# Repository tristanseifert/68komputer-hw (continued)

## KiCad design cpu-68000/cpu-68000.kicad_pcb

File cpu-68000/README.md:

# 68000 CPU Board
This directory contains the schematic and board files for the main 68komputer CPU board, based around a 68000 operating at up to 10MHz. It combines the processor with 1M of RAM and flash ROM and some additional peripherals.

## Peripherals
In addition to the megabyte of boot ROM and RAM available on the board, the following peripherals are available:

- 32K of battery backed NVRAM, which includes a phantom RTC for time keeping
- An [XR68C681](https://www.maxlinear.com/product/interface/uarts/8-bit-vlio-uarts/xr68c681) DUART, compatible with the "legacy" Motorola 68681 part
- I²C master provided by a [PCF8584](https://www.nxp.com/products/interfaces/ic-spi-serial-interface-devices/ic-bus-controller-and-bridge-ics/ic-bus-controller:PCF8584) controller. It's used to access the I2C bus on the backplane.
- Dual SAA1099 PSG audio chips

## Backplane Interface
The backplane interface is just a buffered copy of the 68k's address and data bus, as well as many of its control signals. The direction of buffers on the CPU board are automatically controlled taking into account external bus masters.

As long as external bus masters properly implement the 68000 bus mastering, they will be entirely transparent. All read/write transactions to peripherals implemented on the CPU board itself will be broadcast on the backplane bus to allow external debugging hardware to capture these accesses.

## Programmable Logic
Many of the logic parts of the system are implemented in 22V10C GALs. See the `logic` directory for these files. They can be assembled using [galette.](https://github.com/simon-frankau/galette)

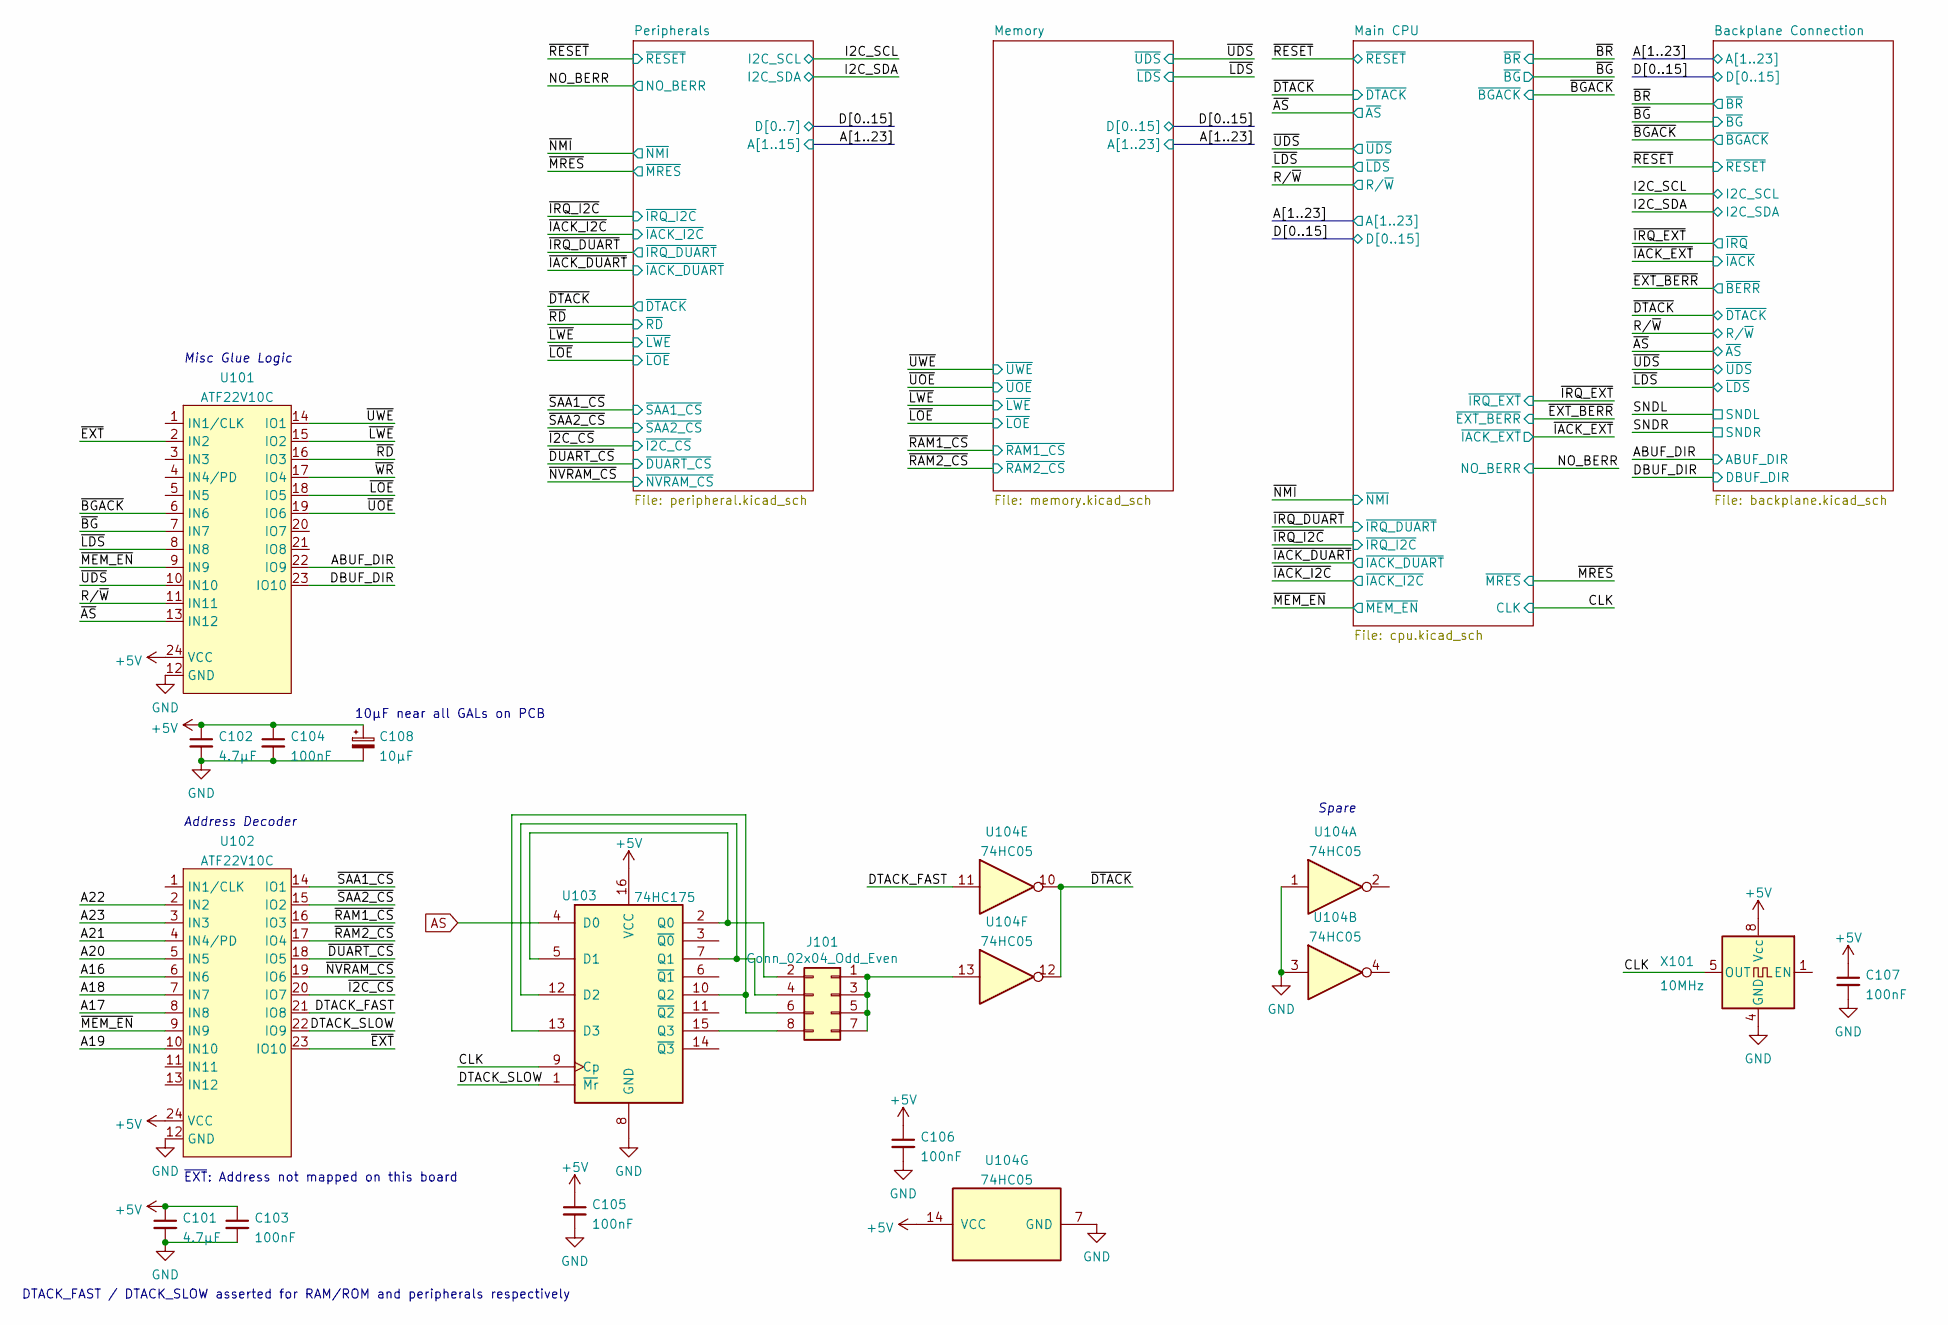
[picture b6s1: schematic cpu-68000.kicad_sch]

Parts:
C101, C102: 4.7µF; C_0805_2012Metric
C103, C104, C105, C106, C107: 100nF; C_0805_2012Metric
C108: 10µF; CP_EIA-3216-18_Kemet-A
J101: Conn_02x04_Odd_Even; PinHeader_2x04_P2.54mm_Vertical
U101, U102: ATF22V10C; DIP-24_W7.62mm_Socket
U103: 74HC175; TSSOP-16_4.4x5mm_P0.65mm; MPN 74HC175PW,118
U104: 74HC05; SOIC-14_3.9x8.7mm_P1.27mm
X101: 10MHz; Oscillator_DIP-8

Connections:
+5V: C101.1, C102.1, C103.1, C104.1, C105.1, C106.1, C107.1, C108.1, U101.24 (VCC), U102.24 (VCC), U103.16 (VCC), U104.14 (VCC), X101.8 (Vcc); also elsewhere on the board
/A16: U102.6 (IN6); also elsewhere on the board
/A17: U102.8 (IN8); also elsewhere on the board
/A18: U102.7 (IN7); also elsewhere on the board
/A19: U102.10 (IN10); also elsewhere on the board
/A20: U102.5 (IN5); also elsewhere on the board
/A21: U102.4 (IN4/PD); also elsewhere on the board
/A22: U102.2 (IN2); also elsewhere on the board
/A23: U102.3 (IN3); also elsewhere on the board
/ABUF_DIR: U101.22 (IO9); also elsewhere on the board
/CLK: U103.9 (Cp), X101.5 (OUT); also elsewhere on the board
/DBUF_DIR: U101.23 (IO10); also elsewhere on the board
/DTACK_FAST: U102.21 (IO8), U104.11
/DTACK_SLOW: U102.22 (IO9), U103.1 (~Mr)
/R/~W: U101.11 (IN11); also elsewhere on the board
/~AS: U101.13 (IN12); also elsewhere on the board
/~BGACK: U101.6 (IN6); also elsewhere on the board
/~BG: U101.7 (IN7); also elsewhere on the board
/~DTACK: U104.10, U104.12; also elsewhere on the board
/~DUART_CS: U102.18 (IO5); also elsewhere on the board
/~EXT: U101.2 (IN2), U102.23 (IO10)
/~I2C_CS: U102.20 (IO7); also elsewhere on the board
/~LDS: U101.8 (IN8); also elsewhere on the board
/~LOE: U101.18 (IO5); also elsewhere on the board
/~LWE: U101.15 (IO2); also elsewhere on the board
/~MEM_EN: U101.9 (IN9), U102.9 (IN9); also elsewhere on the board
/~NVRAM_CS: U102.19 (IO6); also elsewhere on the board
/~RAM1_CS: U102.16 (IO3); also elsewhere on the board
/~RAM2_CS: U102.17 (IO4); also elsewhere on the board
/~RD: U101.16 (IO3)
/~SAA1_CS: U102.14 (IO1); also elsewhere on the board
/~SAA2_CS: U102.15 (IO2); also elsewhere on the board
/~UDS: U101.10 (IN10); also elsewhere on the board
/~UOE: U101.19 (IO6); also elsewhere on the board
/~UWE: U101.14 (IO1); also elsewhere on the board
/~WR: U101.17 (IO4)
AS: U103.4 (D0); also elsewhere on the board
GND: C101.2, C102.2, C103.2, C104.2, C105.2, C106.2, C107.2, C108.2, U101.12 (GND), U102.12 (GND), U103.8 (GND), U104.1, U104.3, U104.7 (GND), X101.4 (GND); also elsewhere on the board
unnamed: J101.1, J101.3, J101.5, J101.7, U104.13
unnamed: J101.2, U103.2 (Q0), U103.5 (D1)
unnamed: J101.4, U103.7 (Q1), U103.12 (D2)
unnamed: J101.6, U103.10 (Q2), U103.13 (D3)
unnamed: J101.8, U103.15 (Q3)

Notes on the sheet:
Address Decoder
~{EXT}: Address not mapped on this board
Spare
Misc Glue Logic
10µF near all GALs on PCB
DTACK_FAST / DTACK_SLOW asserted for RAM/ROM and peripherals respectively

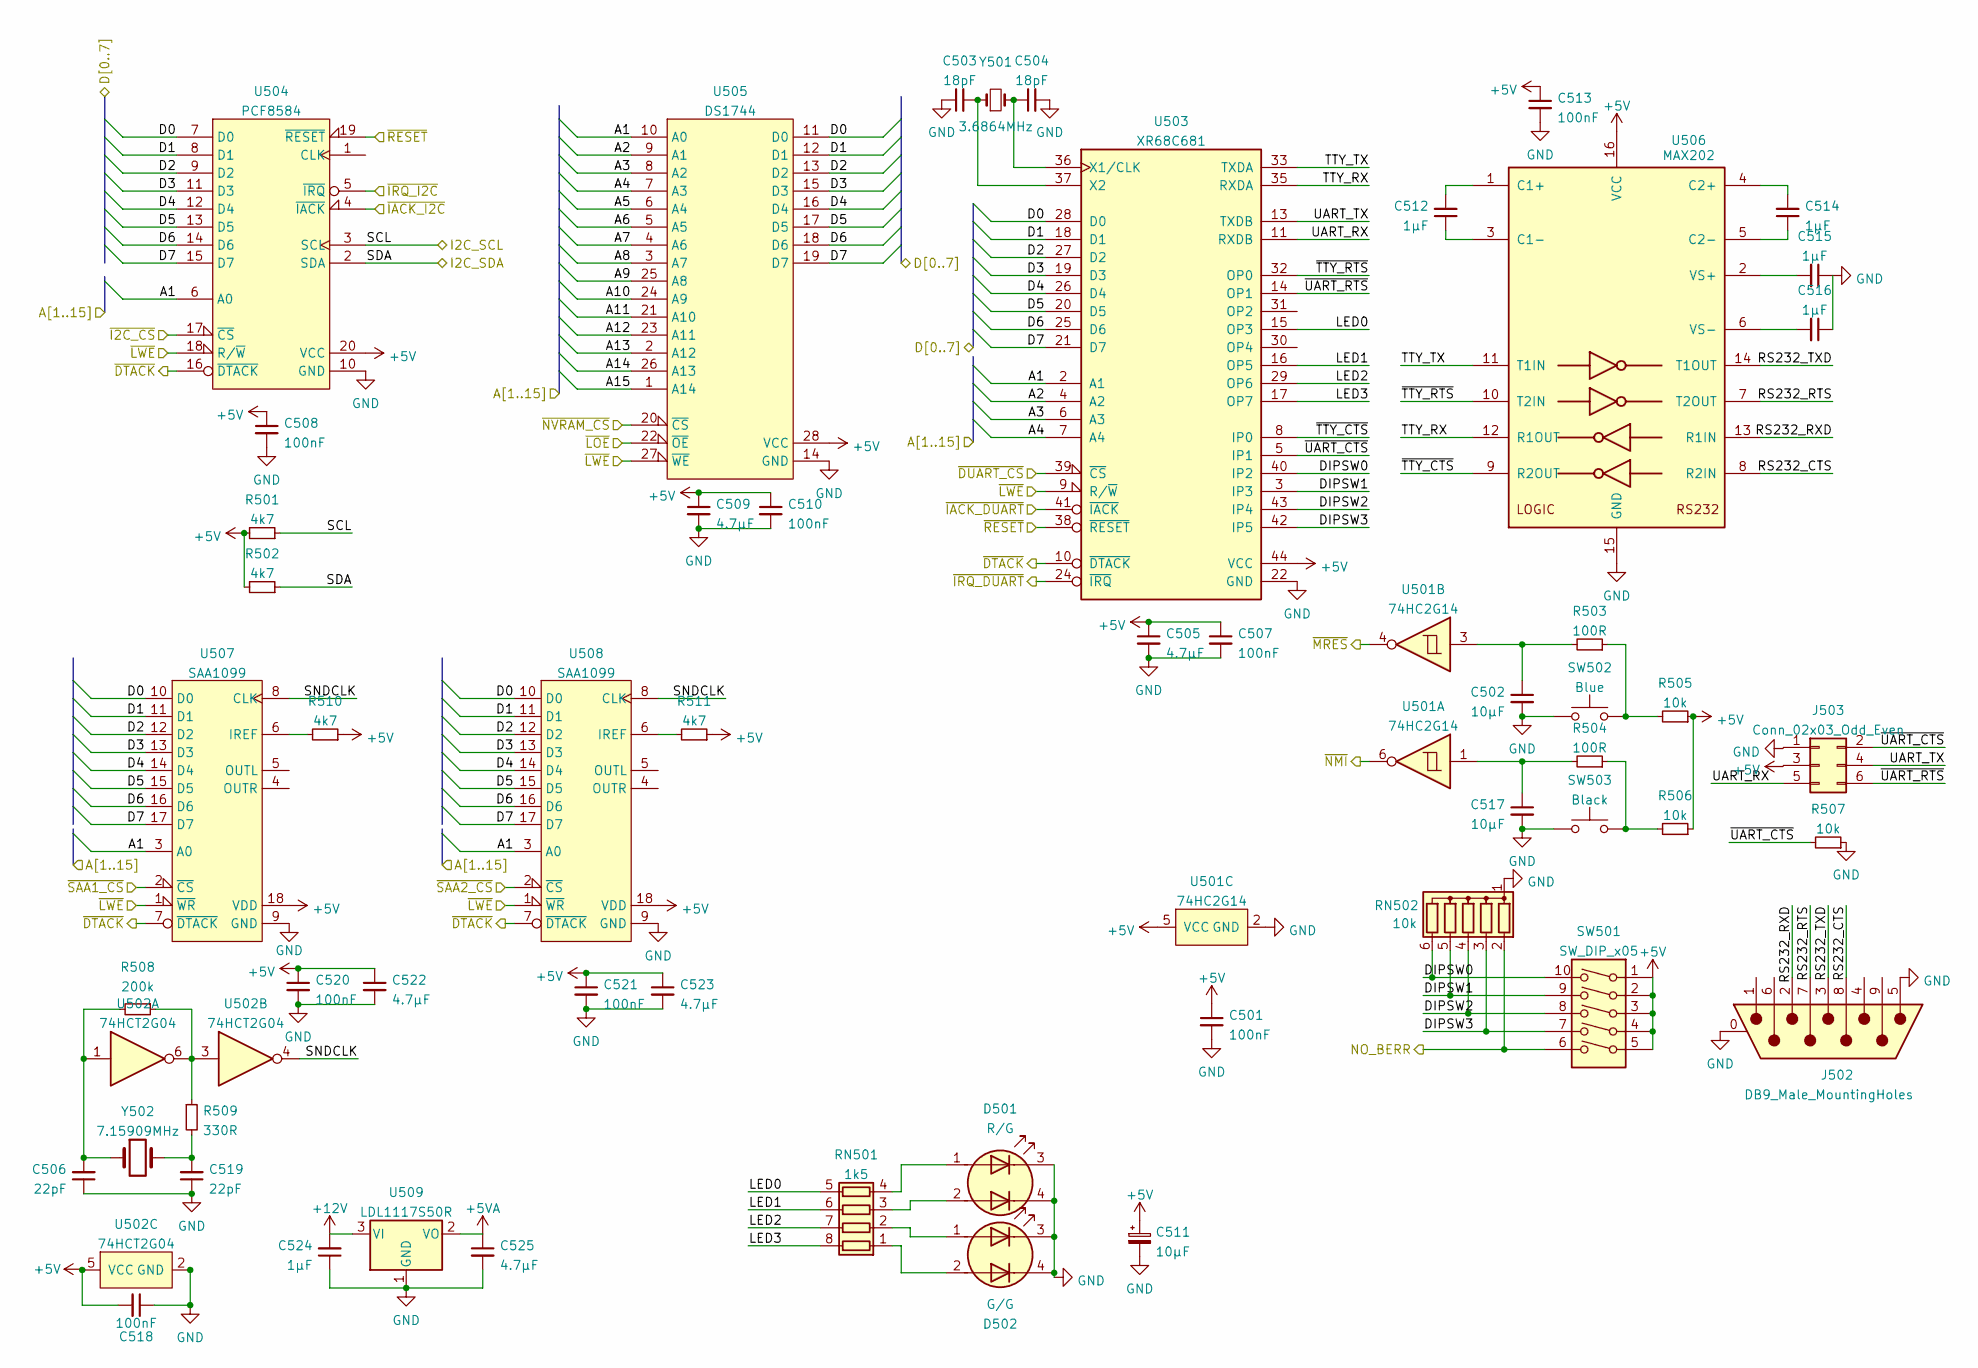
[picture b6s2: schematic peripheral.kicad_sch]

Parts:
C501, C507, C508, C510, C513, C518, C520, C521: 100nF; C_0805_2012Metric
C502, C511, C517: 10µF; C_0805_2012Metric
C503, C504: 18pF; C_0805_2012Metric
C505, C509, C522, C523, C525: 4.7µF; C_0805_2012Metric
C506, C519: 22pF; C_0805_2012Metric
C512, C514, C515, C516, C524: 1µF; C_0805_2012Metric
D501: R/G; H201Cxx; MPN H201CGHDL
D502: G/G; H201Cxx; MPN H201CGDL
J502: DB9_Male_MountingHoles; DSUB-9_Male_Horizontal_P2.77x2.84mm_EdgePinOffset7.70mm_Hou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; MPN K22X-E9P-N-99
J503: Conn_02x03_Odd_Even; PinHeader_2x03_P2.54mm_Horizontal
R501, R502, R510, R511: 4k7; R_0805_2012Metric
R503, R504: 100R; R_0805_2012Metric
R505, R506, R507: 10k; R_0805_2012Metric
R508: 200k; R_0805_2012Metric
R509: 330R; R_0805_2012Metric
RN501: 1k5; R_Array_Convex_4x1206; MPN YC164-JR-071K1L
RN502: 10k; R_Array_SIP6; MPN 4606X-101-103LF
SW501: SW_DIP_x05; SW_DIP_SPSTx05_Piano_10.8x14.26mm_W7.62mm_P2.54mm; MPN DS02C-254-1L-05BE
SW502: Blue; SW_Tactile_SPST_Angled_PTS645Vx83-2LFS; MPN PTS645VM832LFS
SW503: Black; SW_Tactile_SPST_Angled_PTS645Vx83-2LFS; MPN PTS645VH832LFS
U501: 74HC2G14; TSOP-6_1.65x3.05mm_P0.95mm
U502: 74HCT2G04; TSOP-6_1.65x3.05mm_P0.95mm
U503: XR68C681; PLCC-44_THT-Socket
U504: PCF8584; SO-20_12.8x7.5mm_P1.27mm
U505: DS1744; DIP-28_W15.24mm_Socket
U506: MAX202; TSSOP-16_4.4x5mm_P0.65mm; MPN MAX202IPW
U507, U508: SAA1099; DIP-18_W7.62mm_Socket
U509: LDL1117S50R; SOT-223-3_TabPin2
Y501: 3.6864MHz; Crystal_HC49-4H_Vertical; MPN ABL-3.6864MHZ-B2
Y502: 7.15909MHz; Crystal_HC49-4H_Vertical; MPN LFXTAL012626Bulk

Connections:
+5V: C501.1, C505.1, C507.1, C508.1, C509.1, C510.1, C511.1, C513.1, C518.2, C520.1, C521.1, C522.1, C523.1, R501.2, R502.2, R505.1, R506.1, R510.1, R511.1, SW501.1, SW501.2, SW501.3, SW501.4, SW501.5, U501.5 (VCC), U502.5 (VCC), U503.44 (VCC), U504.20 (VCC), U505.28 (VCC), U506.16 (VCC), U507.18 (VDD), U508.18 (VDD); also elsewhere on the board
+5VA: C525.1, U509.2 (VO)
+12V: C524.2, U509.3 (VI); also elsewhere on the board
/A1: U503.2 (A1), U504.6 (A0), U505.10 (A0), U507.3 (A0), U508.3 (A0); also elsewhere on the board
/A2: U503.4 (A2), U505.9 (A1); also elsewhere on the board
/A3: U503.6 (A3), U505.8 (A2); also elsewhere on the board
/A4: U503.7 (A4), U505.7 (A3); also elsewhere on the board
/A5: U505.6 (A4); also elsewhere on the board
/A6: U505.5 (A5); also elsewhere on the board
/A7: U505.4 (A6); also elsewhere on the board
/A8: U505.3 (A7); also elsewhere on the board
/A9: U505.25 (A8); also elsewhere on the board
/A10: U505.24 (A9); also elsewhere on the board
/A11: U505.21 (A10); also elsewhere on the board
/A12: U505.23 (A11); also elsewhere on the board
/A13: U505.2 (A12); also elsewhere on the board
/A14: U505.26 (A13); also elsewhere on the board
/A15: U505.1 (A14); also elsewhere on the board
/D0: U503.28 (D0), U504.7 (D0), U505.11 (D0), U507.10 (D0), U508.10 (D0); also elsewhere on the board
/D1: U503.18 (D1), U504.8 (D1), U505.12 (D1), U507.11 (D1), U508.11 (D1); also elsewhere on the board
/D2: U503.27 (D2), U504.9 (D2), U505.13 (D2), U507.12 (D2), U508.12 (D2); also elsewhere on the board
/D3: U503.19 (D3), U504.11 (D3), U505.15 (D3), U507.13 (D3), U508.13 (D3); also elsewhere on the board
/D4: U503.26 (D4), U504.12 (D4), U505.16 (D4), U507.14 (D4), U508.14 (D4); also elsewhere on the board
/D5: U503.20 (D5), U504.13 (D5), U505.17 (D5), U507.15 (D5), U508.15 (D5); also elsewhere on the board
/D6: U503.25 (D6), U504.14 (D6), U505.18 (D6), U507.16 (D6), U508.16 (D6); also elsewhere on the board
/D7: U503.21 (D7), U504.15 (D7), U505.19 (D7), U507.17 (D7), U508.17 (D7); also elsewhere on the board
/I2C_SCL: R501.1, U504.3 (SCL); also elsewhere on the board
/I2C_SDA: R502.1, U504.2 (SDA); also elsewhere on the board
/NO_BERR: RN502.2 (R1), SW501.6; also elsewhere on the board
/Peripherals/DIPSW0: RN502.6 (R5), SW501.10, U503.40 (IP2)
/Peripherals/DIPSW1: RN502.5 (R4), SW501.9, U503.3 (IP3)
/Peripherals/DIPSW2: RN502.4 (R3), SW501.8, U503.43 (IP4)
/Peripherals/DIPSW3: RN502.3 (R2), SW501.7, U503.42 (IP5)
/Peripherals/LED0: RN501.5 (R4.2), U503.15 (OP3)
/Peripherals/LED1: RN501.6 (R3.2), U503.16 (OP5)
/Peripherals/LED2: RN501.7 (R2.2), U503.29 (OP6)
/Peripherals/LED3: RN501.8 (R1.2), U503.17 (OP7)
/Peripherals/RS232_CTS: J502.8, U506.8 (R2IN)
/Peripherals/RS232_RTS: J502.7, U506.7 (T2OUT)
/Peripherals/RS232_RXD: J502.2, U506.13 (R1IN)
/Peripherals/RS232_TXD: J502.3, U506.14 (T1OUT)
/Peripherals/SNDCLK: U502.4, U507.8 (CLK), U508.8 (CLK)
/Peripherals/TTY_RX: U503.35 (RXDA), U506.12 (R1OUT)
/Peripherals/TTY_TX: U503.33 (TXDA), U506.11 (T1IN)
/Peripherals/UART_RX: J503.5, U503.11 (RXDB)
/Peripherals/UART_TX: J503.4, U503.13 (TXDB)
/Peripherals/~TTY_CTS: U503.8 (IP0), U506.9 (R2OUT)
/Peripherals/~TTY_RTS: U503.32 (OP0), U506.10 (T2IN)
/Peripherals/~UART_CTS: J503.2, R507.2, U503.5 (IP1)
/Peripherals/~UART_RTS: J503.6, U503.14 (OP1)
/~DTACK: U503.10 (~DTACK), U504.16 (~DTACK), U507.7 (~DTACK), U508.7 (~DTACK); also elsewhere on the board
/~DUART_CS: U503.39 (~CS); also elsewhere on the board
/~I2C_CS: U504.17 (~CS); also elsewhere on the board
/~IACK_DUART: U503.41 (~IACK); also elsewhere on the board
/~IACK_I2C: U504.4 (~IACK); also elsewhere on the board
/~IRQ_DUART: U503.24 (~IRQ); also elsewhere on the board
/~IRQ_I2C: U504.5 (~IRQ); also elsewhere on the board
/~LOE: U505.22 (~OE); also elsewhere on the board
/~LWE: U503.9 (R/~W), U504.18 (R/~W), U505.27 (~WE), U507.1 (~WR), U508.1 (~WR); also elsewhere on the board
/~MRES: U501.4; also elsewhere on the board
/~NMI: U501.6; also elsewhere on the board
/~NVRAM_CS: U505.20 (~CS); also elsewhere on the board
/~RESET: U503.38 (~RESET), U504.19 (~RESET); also elsewhere on the board
/~SAA1_CS: U507.2 (~CS); also elsewhere on the board
/~SAA2_CS: U508.2 (~CS); also elsewhere on the board
GND: C501.2, C502.2, C503.1, C504.2, C505.2, C506.1, C507.2, C508.2, C509.2, C510.2, C511.2, C513.2, C515.1, C516.1, C517.2, C518.1, C519.1, C520.2, C521.2, C522.2, C523.2, C524.1, C525.2, D501.3 (K1), D501.4 (K2), D502.3 (K1), D502.4 (K2), J502.0 (PAD), J502.5, R507.1, RN502.1 (common), SW502.1, SW503.1, U501.2 (GND), U502.2 (GND), U503.22 (GND), U504.10 (GND), U505.14 (GND), U506.15 (GND), U507.9 (GND), U508.9 (GND), U509.1 (GND); also elsewhere on the board
unnamed: C502.1, R503.2, U501.3
unnamed: C503.2, U503.37 (X2), Y501.1
unnamed: C504.1, U503.36 (X1/CLK), Y501.2
unnamed: C506.2, R508.2, U502.1, Y502.1
unnamed: C512.1, U506.3 (C1-)
unnamed: C512.2, U506.1 (C1+)
unnamed: C514.1, U506.5 (C2-)
unnamed: C514.2, U506.4 (C2+)
unnamed: C515.2, U506.2 (VS+)
unnamed: C516.2, U506.6 (VS-)
unnamed: C517.1, R504.2, U501.1
unnamed: C519.2, R509.2, Y502.2
unnamed: D501.1 (A1), RN501.4 (R4.1)
unnamed: D501.2 (A2), RN501.3 (R3.1)
unnamed: D502.1 (A1), RN501.2 (R2.1)
unnamed: D502.2 (A2), RN501.1 (R1.1)
unnamed: R503.1, R505.2, SW502.2
unnamed: R504.1, R506.2, SW503.2
unnamed: R508.1, R509.1, U502.3, U502.6
unnamed: R510.2, U507.6 (IREF)
unnamed: R511.2, U508.6 (IREF)

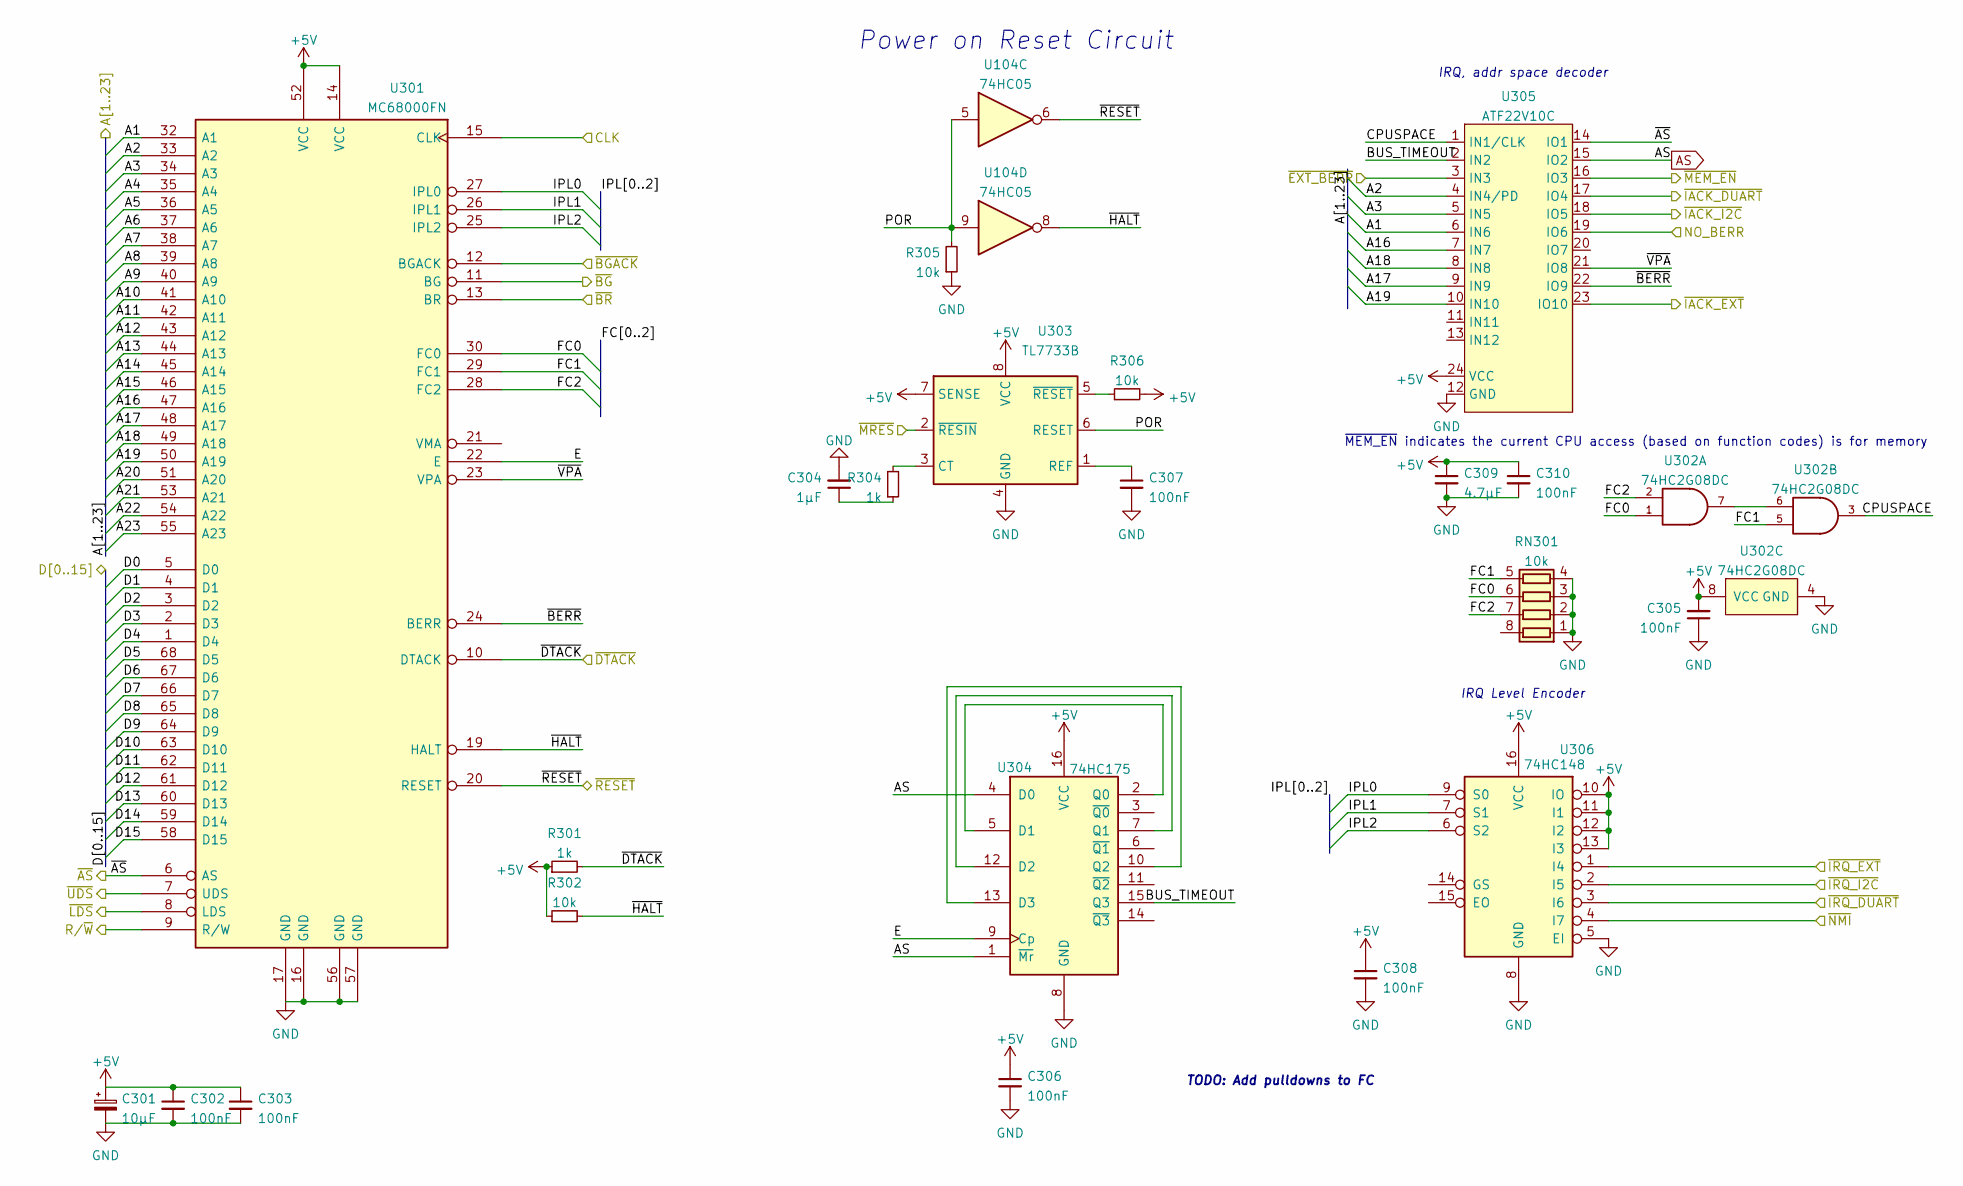
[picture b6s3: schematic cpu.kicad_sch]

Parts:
C301: 10µF; CP_EIA-3216-18_Kemet-A
C302, C303, C305, C306, C307, C308, C310: 100nF; C_0805_2012Metric
C304: 1µF; C_0805_2012Metric
C309: 4.7µF; C_0805_2012Metric
R301, R304: 1k; R_0805_2012Metric
R302, R305, R306: 10k; R_0805_2012Metric
RN301: 10k; R_Array_Convex_4x1206; MPN YC164-FR-0710KL
U104: 74HC05; SOIC-14_3.9x8.7mm_P1.27mm
U301: MC68000FN; PLCC-68_THT-Socket
U302: 74HC2G08DC; VSSOP-8_2.3x2mm_P0.5mm
U303: TL7733B; SOIC-8_3.9x4.9mm_P1.27mm
U304: 74HC175; TSSOP-16_4.4x5mm_P0.65mm; MPN 74HC175PW,118
U305: ATF22V10C; DIP-24_W7.62mm_Socket
U306: 74HC148; SOIC-16_3.9x9.9mm_P1.27mm

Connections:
+5V: C301.1, C302.1, C303.1, C305.2, C306.1, C308.1, C309.1, C310.1, R301.1, R302.1, R306.2, U301.14 (VCC), U301.52 (VCC), U302.8 (VCC), U303.7 (SENSE), U303.8 (VCC), U304.16 (VCC), U305.24 (VCC), U306.10 (IO), U306.11 (I1), U306.12 (I2), U306.13 (I3), U306.16 (VCC); also elsewhere on the board
/A1: U301.32 (A1), U305.6 (IN6); also elsewhere on the board
/A2: U301.33 (A2), U305.4 (IN4/PD); also elsewhere on the board
/A3: U301.34 (A3), U305.5 (IN5); also elsewhere on the board
/A4: U301.35 (A4); also elsewhere on the board
/A5: U301.36 (A5); also elsewhere on the board
/A6: U301.37 (A6); also elsewhere on the board
/A7: U301.38 (A7); also elsewhere on the board
/A8: U301.39 (A8); also elsewhere on the board
/A9: U301.40 (A9); also elsewhere on the board
/A10: U301.41 (A10); also elsewhere on the board
/A11: U301.42 (A11); also elsewhere on the board
/A12: U301.43 (A12); also elsewhere on the board
/A13: U301.44 (A13); also elsewhere on the board
/A14: U301.45 (A14); also elsewhere on the board
/A15: U301.46 (A15); also elsewhere on the board
/A16: U301.47 (A16), U305.7 (IN7); also elsewhere on the board
/A17: U301.48 (A17), U305.9 (IN9); also elsewhere on the board
/A18: U301.49 (A18), U305.8 (IN8); also elsewhere on the board
/A19: U301.50 (A19), U305.10 (IN10); also elsewhere on the board
/A20: U301.51 (A20); also elsewhere on the board
/A21: U301.53 (A21); also elsewhere on the board
/A22: U301.54 (A22); also elsewhere on the board
/A23: U301.55 (A23); also elsewhere on the board
/CLK: U301.15 (CLK); also elsewhere on the board
/D0: U301.5 (D0); also elsewhere on the board
/D1: U301.4 (D1); also elsewhere on the board
/D2: U301.3 (D2); also elsewhere on the board
/D3: U301.2 (D3); also elsewhere on the board
/D4: U301.1 (D4); also elsewhere on the board
/D5: U301.68 (D5); also elsewhere on the board
/D6: U301.67 (D6); also elsewhere on the board
/D7: U301.66 (D7); also elsewhere on the board
/D8: U301.65 (D8); also elsewhere on the board
/D9: U301.64 (D9); also elsewhere on the board
/D10: U301.63 (D10); also elsewhere on the board
/D11: U301.62 (D11); also elsewhere on the board
/D12: U301.61 (D12); also elsewhere on the board
/D13: U301.60 (D13); also elsewhere on the board
/D14: U301.59 (D14); also elsewhere on the board
/D15: U301.58 (D15); also elsewhere on the board
/Main CPU/BUS_TIMEOUT: U304.15 (Q3), U305.2 (IN2)
/Main CPU/CPUSPACE: U302.3, U305.1 (IN1/CLK)
/Main CPU/E: U301.22 (E), U304.9 (Cp)
/Main CPU/FC0: RN301.6 (R3.2), U301.30 (FC0), U302.1
/Main CPU/FC1: RN301.5 (R4.2), U301.29 (FC1), U302.5
/Main CPU/FC2: RN301.7 (R2.2), U301.28 (FC2), U302.2
/Main CPU/IPL0: U301.27 (IPL0), U306.9 (S0)
/Main CPU/IPL1: U301.26 (IPL1), U306.7 (S1)
/Main CPU/IPL2: U301.25 (IPL2), U306.6 (S2)
/Main CPU/POR: R305.2, U104.5, U104.9, U303.6 (RESET)
/Main CPU/~BERR: U301.24 (BERR), U305.22 (IO9)
/Main CPU/~HALT: R302.2, U104.8, U301.19 (HALT)
/Main CPU/~VPA: U301.23 (VPA), U305.21 (IO8)
/NO_BERR: U305.19 (IO6); also elsewhere on the board
/R/~W: U301.9 (R/W); also elsewhere on the board
/~AS: U301.6 (AS), U305.14 (IO1); also elsewhere on the board
/~BGACK: U301.12 (BGACK); also elsewhere on the board
/~BG: U301.11 (BG); also elsewhere on the board
/~BR: U301.13 (BR); also elsewhere on the board
/~DTACK: R301.2, U301.10 (DTACK); also elsewhere on the board
/~EXT_BERR: U305.3 (IN3); also elsewhere on the board
/~IACK_DUART: U305.17 (IO4); also elsewhere on the board
/~IACK_EXT: U305.23 (IO10); also elsewhere on the board
/~IACK_I2C: U305.18 (IO5); also elsewhere on the board
/~IRQ_DUART: U306.3 (I6); also elsewhere on the board
/~IRQ_EXT: U306.1 (I4); also elsewhere on the board
/~IRQ_I2C: U306.2 (I5); also elsewhere on the board
/~LDS: U301.8 (LDS); also elsewhere on the board
/~MEM_EN: U305.16 (IO3); also elsewhere on the board
/~MRES: U303.2 (~RESIN); also elsewhere on the board
/~NMI: U306.4 (I7); also elsewhere on the board
/~RESET: U104.6, U301.20 (RESET); also elsewhere on the board
/~UDS: U301.7 (UDS); also elsewhere on the board
AS: U304.1 (~Mr), U304.4 (D0), U305.15 (IO2); also elsewhere on the board
GND: C301.2, C302.2, C303.2, C304.2, C305.1, C306.2, C307.2, C308.2, C309.2, C310.2, R305.1, RN301.1 (R1.1), RN301.2 (R2.1), RN301.3 (R3.1), RN301.4 (R4.1), U301.16 (GND), U301.17 (GND), U301.56 (GND), U301.57 (GND), U302.4 (GND), U303.4 (GND), U304.8 (GND), U305.12 (GND), U306.5 (EI), U306.8 (GND); also elsewhere on the board
unnamed: C304.1, R304.1
unnamed: C307.1, U303.1 (REF)
unnamed: R304.2, U303.3 (CT)
unnamed: R306.1, U303.5 (~RESET)
unnamed: U302.6, U302.7
unnamed: U304.2 (Q0), U304.5 (D1)
unnamed: U304.10 (Q2), U304.13 (D3)
unnamed: U304.7 (Q1), U304.12 (D2)

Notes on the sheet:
TODO: Add pulldowns to FC
IRQ, addr space decoder
~{MEM_EN} indicates the current CPU access (based on function codes) is for memory
IRQ Level Encoder
Power on Reset Circuit
